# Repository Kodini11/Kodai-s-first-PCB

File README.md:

# Kodai's Thingy

## The Lore
I'm a high school student just beginning to learn how to build stuff. I came across an Instagram reel talking about Hackclub and I was interested so I decided to attempt this project. I've never used Fusion 360 and KiCAD before so this was definitely a learning experience. In all honesty, I followed the tutorial 1:1 just because I wanted to avoid complexities since this is my first time. However, I am definitely willing to make stuff of my own in the future!

## Use Case
This hackpad is meant to be used to help me animate in Blender. I created a hackpad using 4 switches, 1 rp2040, and 2 leds.

## BOM
- 4x Cherry MX Switches
- 2x SK6812 MINI Leds
- 1x XIAO RP2040
- 4x Blank DSA Keycaps
- 4x M3x16 Bolt
- 4x M3 Heatset

## Additional Items
- KMK firmware
- Top Case.stl
- Bottom Case.stl

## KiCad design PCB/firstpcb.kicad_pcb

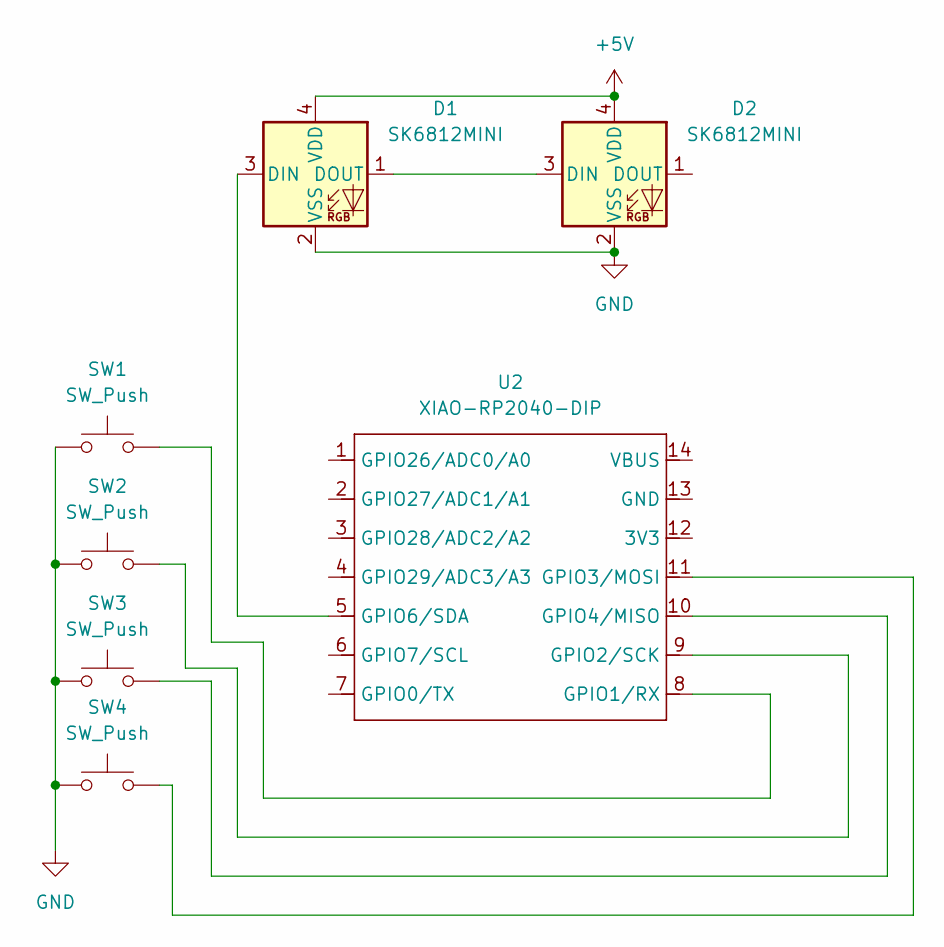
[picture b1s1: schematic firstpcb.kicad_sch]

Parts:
D1, D2: SK6812MINI; LED_SK6812MINI_PLCC4_3.5x3.5mm_P1.75mm
SW1, SW2, SW3, SW4: SW_Push; SW_Cherry_MX_1.00u_PCB
U2: XIAO-RP2040-DIP

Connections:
+5V: D1.4 (VDD), D2.4 (VDD)
GND: D1.2 (VSS), D2.2 (VSS), SW1.1, SW2.1, SW3.1, SW4.1
unnamed: D1.3 (DIN), U2.5 (GPIO6/SDA)
unnamed: D1.1 (DOUT), D2.3 (DIN)
unnamed: SW1.2, U2.8 (GPIO1/RX)
unnamed: SW2.2, U2.9 (GPIO2/SCK)
unnamed: SW4.2, U2.11 (GPIO3/MOSI)
unnamed: SW3.2, U2.10 (GPIO4/MISO)

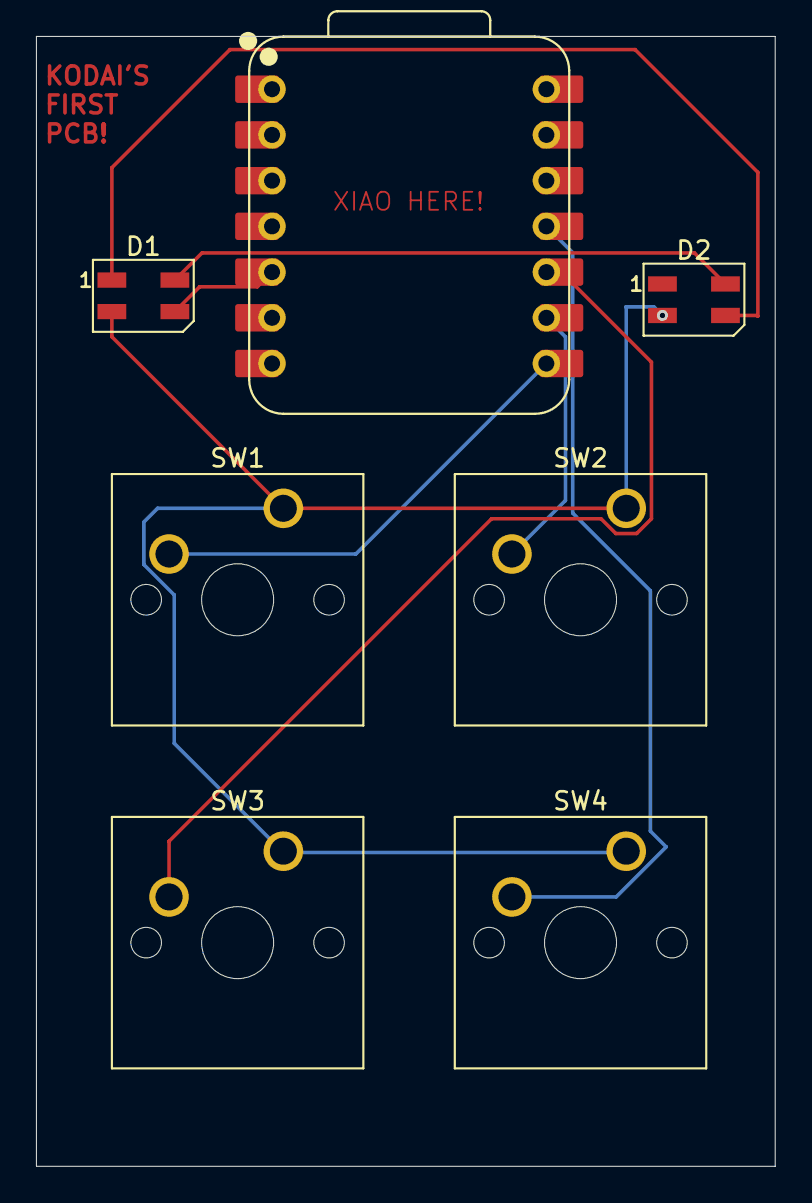
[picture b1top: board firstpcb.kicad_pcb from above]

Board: 2 copper layers, 41.0 x 62.8 mm, 7 parts (0 on the bottom side), 8 nets.

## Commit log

2026-01-17 Kodai's first PCB case.step
2026-01-17 Add KiCad PCB project files
2026-01-17 Add FIRMWARE folder with PCB Firmware.py
2026-01-17 Images into FIRMWARE
2026-01-17 README
2026-01-18 README.md
2026-01-18 Updated README file
2026-01-18 Updated file
